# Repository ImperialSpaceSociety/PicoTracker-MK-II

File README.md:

# Pico Balloon Tracker Version 2.0

## Objectives
This Pico balloon tracker is designed to offer an easy to build and low cost entry for people who want to launch small Helium filled balloons with a small tracking payload.
Ideally, it should be able to fly around the world on board a small balloon.

## License

Hardware is Licensed under CERN OHL v.1.2 or later https://www.ohwr.org/documents/294 No warranty is provided for this documentation implied or otherwise.

Software is licensed under MIT License.

MIT License

Copyright (c) 2018 Imperial College Space Society

Derived Software  Copyright (c) 2014  Richard Meadows <richardeoin>

Permission is hereby granted, free of charge, to any person obtaining a copy of this software and associated documentation files (the "Software"), to deal in the Software without restriction, including without limitation the rights to use, copy, modify, merge, publish, distribute, sublicense, and/or sell copies of the Software, and to permit persons to whom the Software is furnished to do so, subject to the following conditions:

The above copyright notice and this permission notice shall be included in all copies or substantial portions of the Software.

THE SOFTWARE IS PROVIDED "AS IS", WITHOUT WARRANTY OF ANY KIND, EXPRESS OR IMPLIED, INCLUDING BUT NOT LIMITED TO THE WARRANTIES OF MERCHANTABILITY, FITNESS FOR A PARTICULAR PURPOSE AND NONINFRINGEMENT. IN NO EVENT SHALL THE AUTHORS OR COPYRIGHT HOLDERS BE LIABLE FOR ANY CLAIM, DAMAGES OR OTHER LIABILITY, WHETHER IN AN ACTION OF CONTRACT, TORT OR OTHERWISE, ARISING FROM, OUT OF OR IN CONNECTION WITH THE SOFTWARE OR THE USE OR OTHER DEALINGS IN THE SOFTWARE.

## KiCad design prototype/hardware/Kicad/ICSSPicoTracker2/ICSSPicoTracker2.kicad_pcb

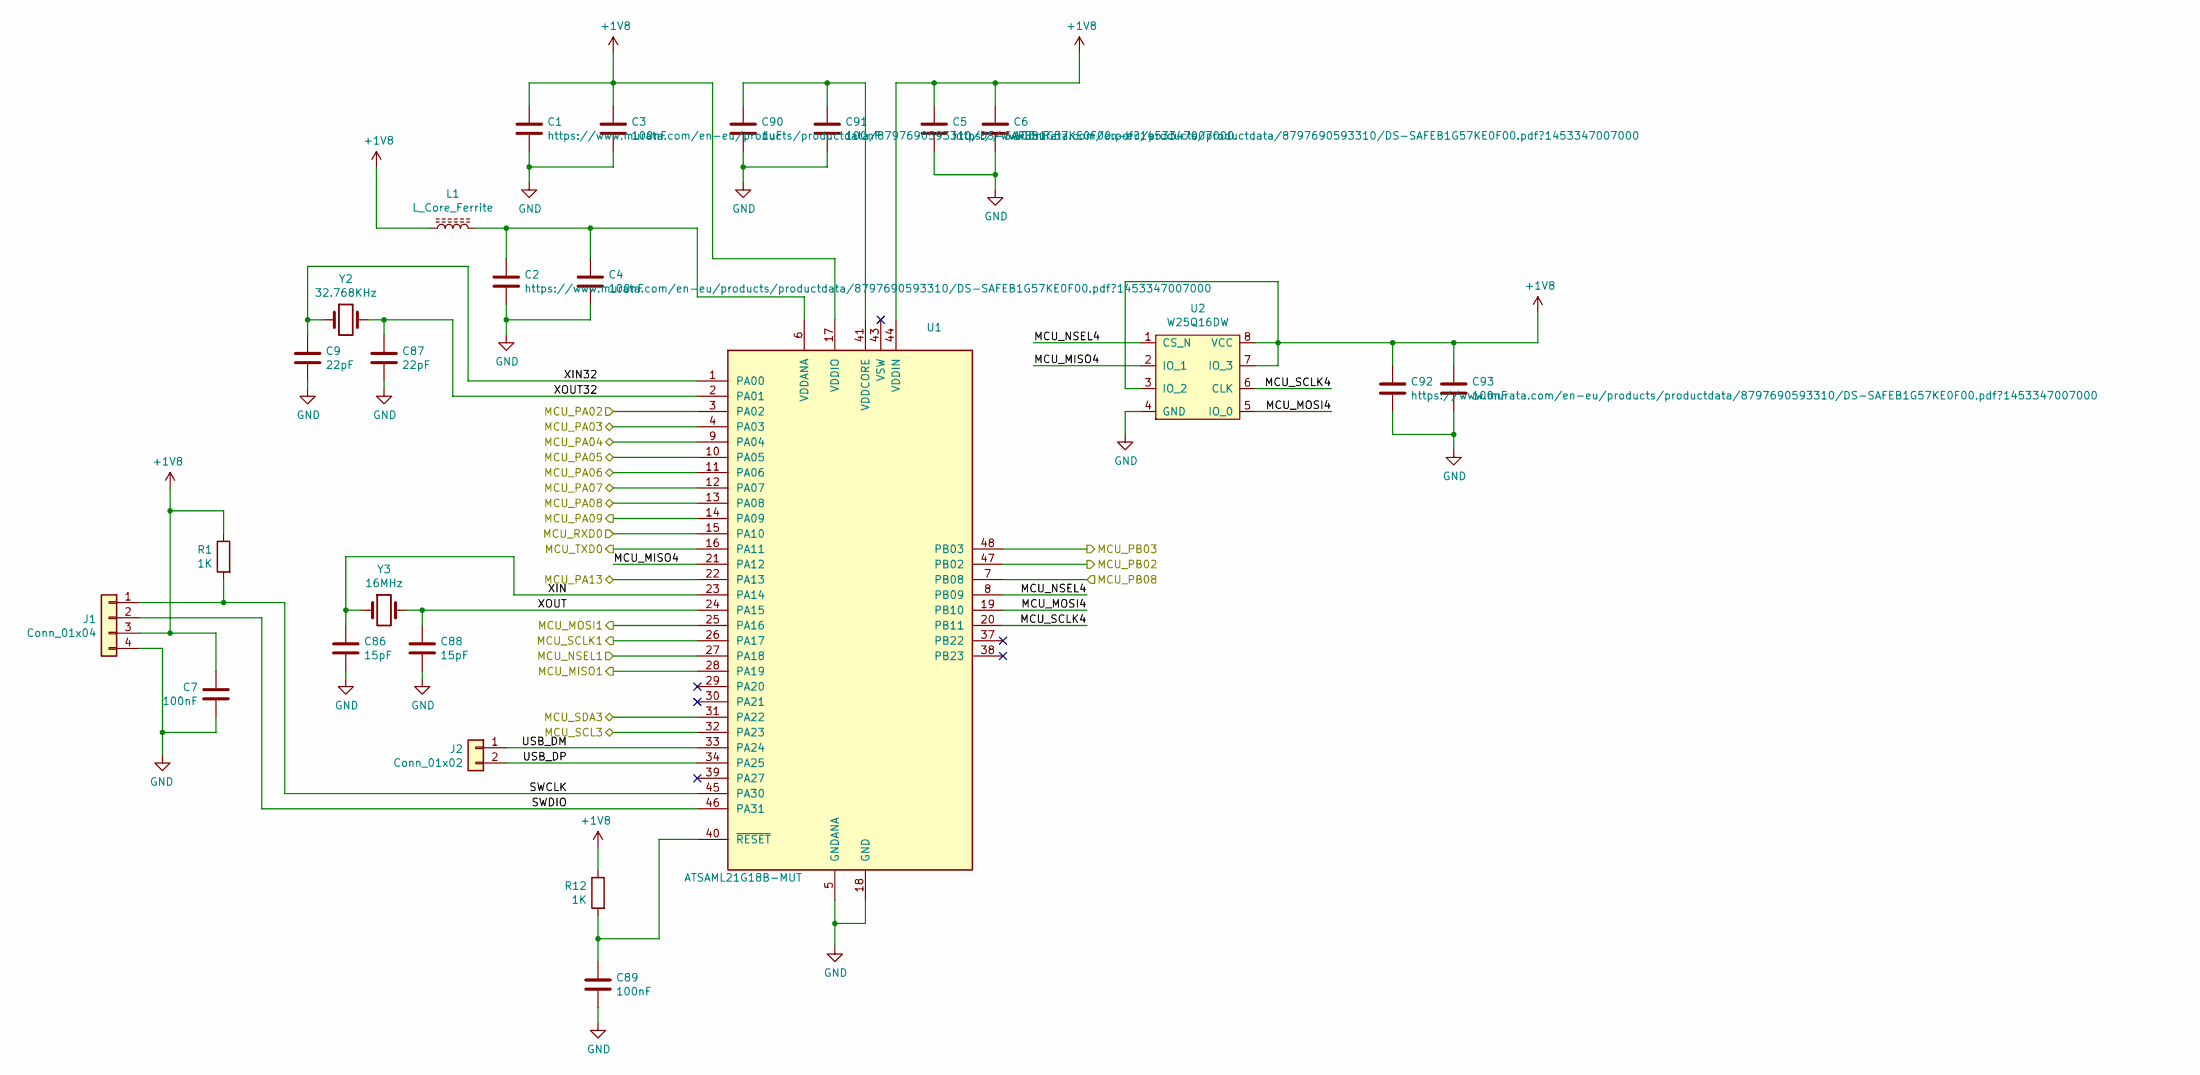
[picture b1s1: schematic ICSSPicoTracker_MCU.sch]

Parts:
C1, C2, C5, C92: https://www.murata.com/en-eu/products/productdata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; C_0603_1608Metric
C3, C4, C6, C7, C89, C91, C93: 100nF; C_0603_1608Metric
C9, C87: 22pF; C_0402_1005Metric
C86, C88: 15pF; C_0402_1005Metric
C90: 1uF; C_0603_1608Metric
J1: Conn_01x04; PinHeader_1x04_P1.00mm_Vertical
J2: Conn_01x02; PinHeader_1x02_P1.00mm_Vertical
L1: L_Core_Ferrite; L_0603_1608Metric
R1, R12: 1K; R_0603_1608Metric
U1: ATSAML21G18B-MUT; QFN-48-1EP_7x7mm_P0.5mm_EP5.15x5.15mm
U2: W25Q16DW; WSON-8-1EP_6x5mm_P1.27mm_EP3.4x4.3mm
Y2: 32.768KHz; Crystal_SMD_2012-2Pin_2.0x1.2mm
Y3: 16MHz; Crystal_SMD_2520-4Pin_2.5x2.0mm

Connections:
+1V8: C1.1, C3.1, C5.1, C6.1, C7.1, C92.1, C93.1, J1.3, L1.1, R1.1, R12.1, U1.17 (VDDIO), U1.36 (VDDIO), U1.44 (VDDIN), U2.3 (IO_2), U2.7 (IO_3), U2.8 (VCC); also elsewhere on the board
/GPS/GPS_1PPS: U1.7 (PB08); also elsewhere on the board
/GPS/GPS_NRES: U1.47 (PB02); also elsewhere on the board
/GPS/GPS_NSAFEBOOT: U1.48 (PB03); also elsewhere on the board
/GPS/GPS_RXD: U1.16 (PA11); also elsewhere on the board
/GPS/GPS_SCL: U1.32 (PA23); also elsewhere on the board
/GPS/GPS_SDA: U1.31 (PA22); also elsewhere on the board
/GPS/GPS_TXD: U1.15 (PA10); also elsewhere on the board
/MCU/MCU_MISO1: U1.28 (PA19); also elsewhere on the board
/MCU/MCU_MISO4: U1.21 (PA12), U2.2 (IO_1)
/MCU/MCU_MOSI1: U1.25 (PA16); also elsewhere on the board
/MCU/MCU_MOSI4: U1.19 (PB10), U2.5 (IO_0)
/MCU/MCU_NSEL1: U1.27 (PA18); also elsewhere on the board
/MCU/MCU_NSEL4: U1.8 (PB09), U2.1 (CS_N)
/MCU/MCU_PA02: U1.3 (PA02); also elsewhere on the board
/MCU/MCU_PA03: U1.4 (PA03); also elsewhere on the board
/MCU/MCU_PA04: U1.9 (PA04); also elsewhere on the board
/MCU/MCU_PA05: U1.10 (PA05); also elsewhere on the board
/MCU/MCU_PA06: U1.11 (PA06); also elsewhere on the board
/MCU/MCU_PA07: U1.12 (PA07); also elsewhere on the board
/MCU/MCU_PA08: U1.13 (PA08); also elsewhere on the board
/MCU/MCU_PA09: U1.14 (PA09); also elsewhere on the board
/MCU/MCU_PA13: U1.22 (PA13); also elsewhere on the board
/MCU/MCU_SCLK1: U1.26 (PA17); also elsewhere on the board
/MCU/MCU_SCLK4: U1.20 (PB11), U2.6 (CLK)
/MCU/SWCLK: J1.1, R1.2, U1.45 (PA30)
/MCU/SWDIO: J1.2, U1.46 (PA31)
/MCU/USB_DM: J2.1, U1.33 (PA24)
/MCU/USB_DP: J2.2, U1.34 (PA25)
/MCU/XIN: C86.1, U1.23 (PA14), Y3.1
/MCU/XIN32: C9.1, U1.1 (PA00), Y2.1
/MCU/XOUT: C88.1, U1.24 (PA15), Y3.2
/MCU/XOUT32: C87.1, U1.2 (PA01), Y2.2
unnamed: C2.1, C4.1, L1.2, U1.6 (VDDANA)
unnamed: C89.1, R12.2, U1.40 (~RESET)
unnamed: C90.1, C91.1, U1.41 (VDDCORE)

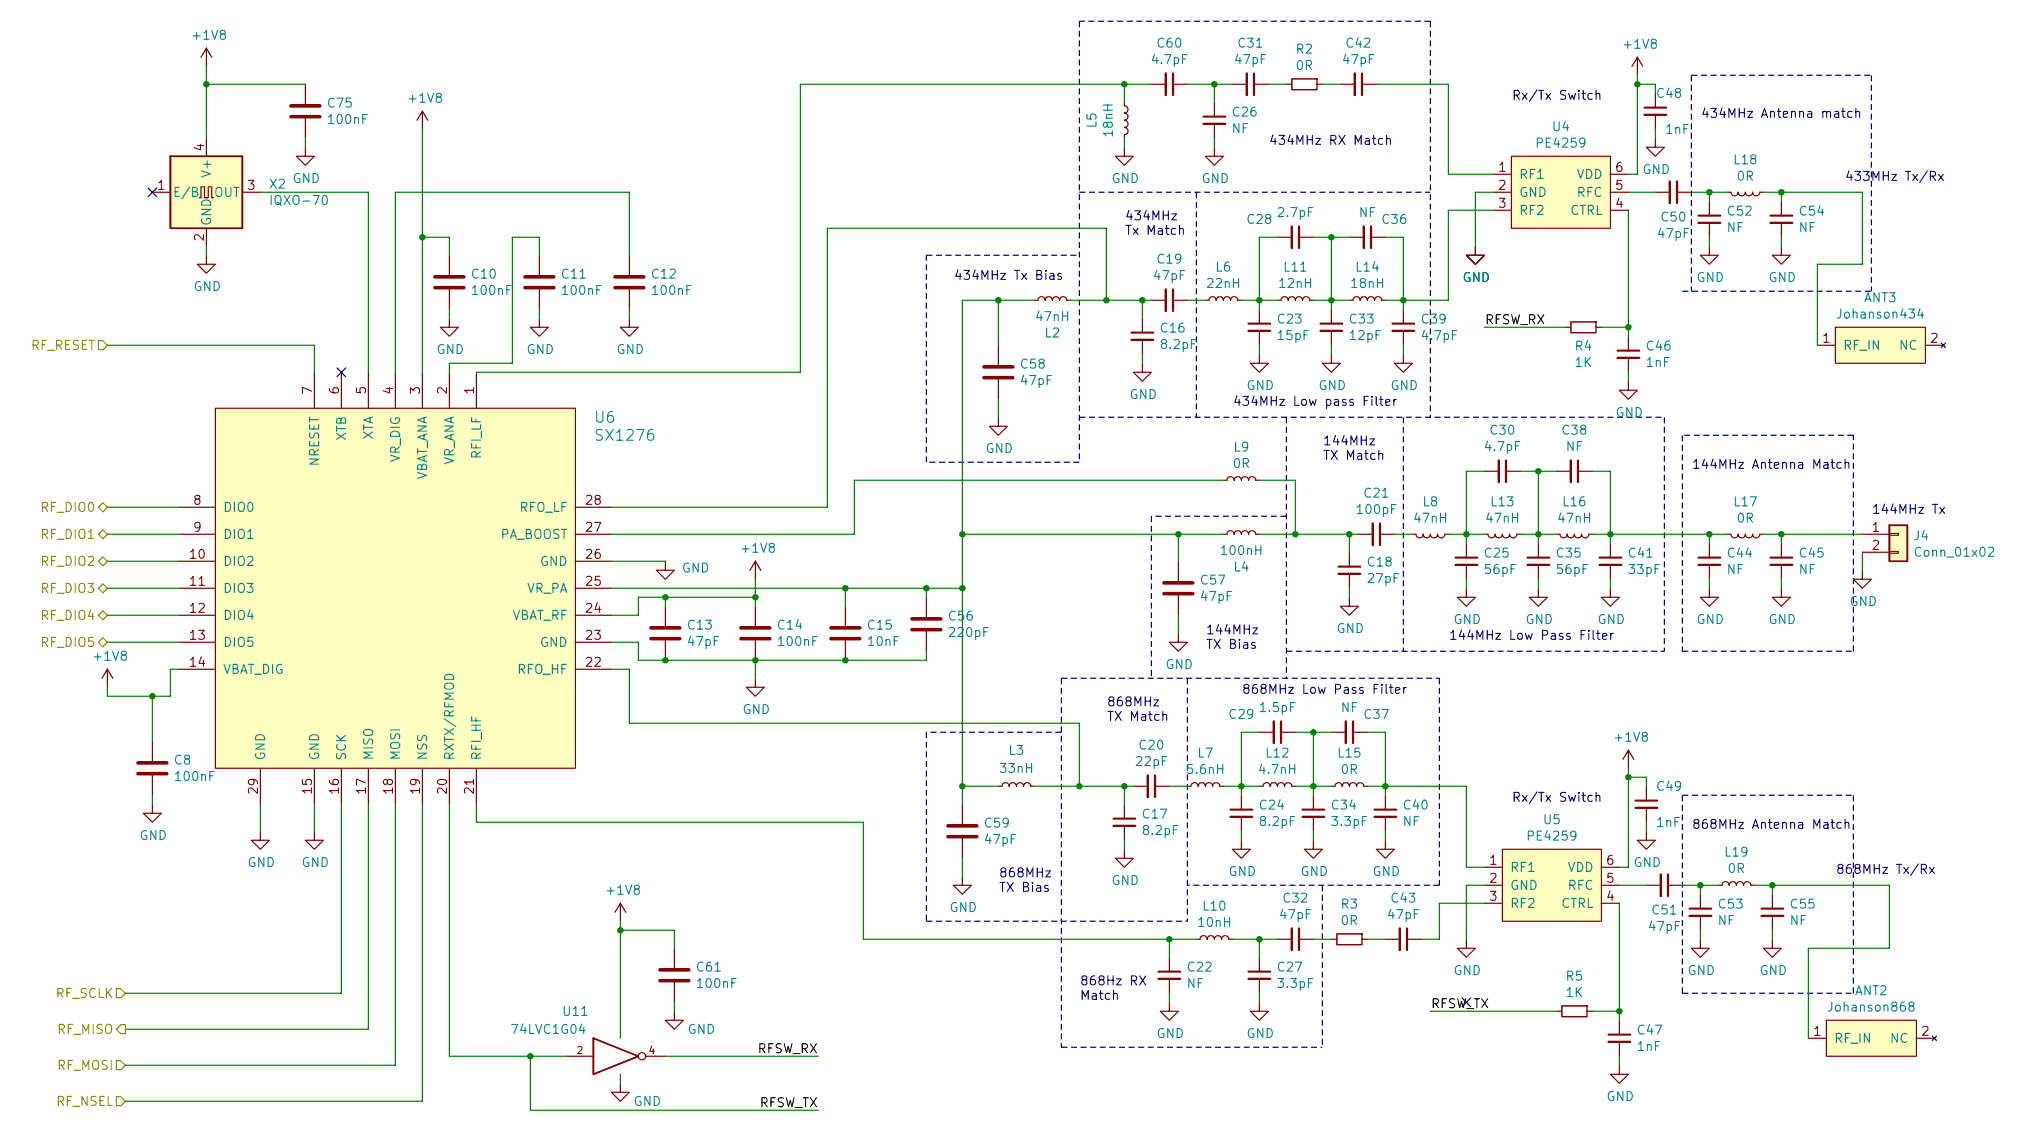
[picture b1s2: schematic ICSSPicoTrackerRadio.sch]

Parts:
ANT2: Johanson868
ANT3: Johanson434
C8, C10, C11, C12, C14, C61, C75: 100nF; C_0603_1608Metric
C13, C19, C31, C32, C42, C43, C50, C51, C57, C58, C59: 47pF; C_0402_1005Metric
C15: 10nF; C_0402_1005Metric
C16, C17, C24: 8.2pF; C_0402_1005Metric
C18: 27pF; C_0402_1005Metric
C20: 22pF; C_0402_1005Metric
C21: 100pF; C_0402_1005Metric
C22, C26, C36, C37, C38, C40, C44, C45, C52, C53, C54, C55: NF; C_0402_1005Metric
C23: 15pF; C_0402_1005Metric
C25, C35: 56pF; C_0402_1005Metric
C27, C34: 3.3pF; C_0402_1005Metric
C28: 2.7pF; C_0402_1005Metric
C29: 1.5pF; C_0402_1005Metric
C30, C39, C60: 4.7pF; C_0402_1005Metric
C33: 12pF; C_0402_1005Metric
C41: 33pF; C_0402_1005Metric
C46, C47, C48, C49: 1nF; C_0402_1005Metric
C56: 220pF; C_0402_1005Metric
J4: Conn_01x02; PinHeader_1x02_P2.54mm_Vertical
L2, L8, L13, L16: 47nH; L_0402_1005Metric
L3: 33nH; L_0402_1005Metric
L4: 100nH; L_0402_1005Metric
L5, L14: 18nH; L_0402_1005Metric
L6: 22nH; L_0402_1005Metric
L7: 5.6nH; L_0402_1005Metric
L9, L15, L17, L18, L19: 0R; L_0402_1005Metric
L10: 10nH; L_0402_1005Metric
L11: 12nH; L_0402_1005Metric
L12: 4.7nH; L_0402_1005Metric
R2, R3: 0R; R_0603_1608Metric
R4, R5: 1K; R_0603_1608Metric
U4, U5: PE4259; SOT-363_SC-70-6_Handsoldering
U6: SX1276; QFN-28-1EP_6x6mm_P0.65mm_EP4.25x4.25mm_ThermalVias
U11: 74LVC1G04; SOT-353_SC-70-5
X2: IQXO-70; Oscillator_SMD_SeikoEpson_SG210-4Pin_2.5x2.0mm

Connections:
+1V8: C8.1, C10.1, C13.1, C14.1, C48.1, C49.1, C61.1, C75.1, U4.6 (VDD), U5.6 (VDD), U6.3 (VBAT_ANA), U6.14 (VBAT_DIG), U6.24 (VBAT_RF), U11.5 (VCC), X2.4 (V+); also elsewhere on the board
/MCU/MCU_MISO1: U6.17 (MISO); also elsewhere on the board
/MCU/MCU_MOSI1: U6.18 (MOSI); also elsewhere on the board
/MCU/MCU_NSEL1: U6.19 (NSS); also elsewhere on the board
/MCU/MCU_PA03: U6.13 (DIO5); also elsewhere on the board
/MCU/MCU_PA04: U6.12 (DIO4); also elsewhere on the board
/MCU/MCU_PA05: U6.11 (DIO3); also elsewhere on the board
/MCU/MCU_PA06: U6.10 (DIO2); also elsewhere on the board
/MCU/MCU_PA07: U6.9 (DIO1); also elsewhere on the board
/MCU/MCU_PA08: U6.8 (DIO0); also elsewhere on the board
/MCU/MCU_PA09: U6.7 (NRESET); also elsewhere on the board
/MCU/MCU_SCLK1: U6.16 (SCK); also elsewhere on the board
/Telemetry Radio/RFSW_RX: R4.2, U11.4
/Telemetry Radio/RFSW_TX: R5.2, U6.20 (RXTX/RFMOD), U11.2
unnamed: ANT2.1 (RF_IN), C55.1, L19.2
unnamed: ANT3.1 (RF_IN), C54.1, L18.2
unnamed: C11.1, U6.2 (VR_ANA)
unnamed: C12.1, U6.4 (VR_DIG)
unnamed: C15.1, C56.1, C57.1, C58.1, C59.1, L2.1, L3.1, L4.1, U6.25 (VR_PA)
unnamed: C16.1, C19.2, L2.2, U6.28 (RFO_LF)
unnamed: C17.1, C20.2, L3.2, U6.22 (RFO_HF)
unnamed: C18.1, C21.2, L4.2, L9.2
unnamed: C19.1, L6.1
unnamed: C20.1, L7.1
unnamed: C21.1, L8.1
unnamed: C22.1, L10.1, U6.21 (RFI_HF)
unnamed: C23.1, C28.2, L6.2, L11.1
unnamed: C24.1, C29.2, L7.2, L12.1
unnamed: C25.1, C30.2, L8.2, L13.1
unnamed: C26.1, C31.2, C60.1
unnamed: C27.1, C32.2, L10.2
unnamed: C28.1, C33.1, C36.2, L11.2, L14.1
unnamed: C29.1, C34.1, C37.2, L12.2, L15.1
unnamed: C30.1, C35.1, C38.2, L13.2, L16.1
unnamed: C31.1, R2.2
unnamed: C32.1, R3.2
unnamed: C36.1, C39.1, L14.2, U4.3 (RF2)
unnamed: C37.1, C40.1, L15.2, U5.1 (RF1)
unnamed: C38.1, C41.1, C44.1, L16.2, L17.2
unnamed: C42.1, U4.1 (RF1)
unnamed: C42.2, R2.1
unnamed: C43.1, U5.3 (RF2)
unnamed: C43.2, R3.1
unnamed: C45.1, J4.1, L17.1
unnamed: C46.1, R4.1, U4.4 (CTRL)
unnamed: C47.1, R5.1, U5.4 (CTRL)
unnamed: C50.1, C52.1, L18.1
unnamed: C50.2, U4.5 (RFC)
unnamed: C51.1, C53.1, L19.1
unnamed: C51.2, U5.5 (RFC)
unnamed: C60.2, L5.1, U6.1 (RFI_LF)
unnamed: L9.1, U6.27 (PA_BOOST)
unnamed: U6.5 (XTA), X2.3 (OUT)

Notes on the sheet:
144MHz Tx
433MHz Tx/Rx
868MHz Tx/Rx
144MHz Low Pass Filter
144MHz Antenna Match
144MHz TX Bias
144MHz TX Match
Rx/Tx Switch
868MHz TX Bias
868MHz TX Match
868MHz Low Pass Filter
868MHz Antenna Match
434MHz RX Match
434MHz Tx Bias
434MHz Tx Match
434MHz Low pass Filter
434MHz Antenna match
868Hz RX Match

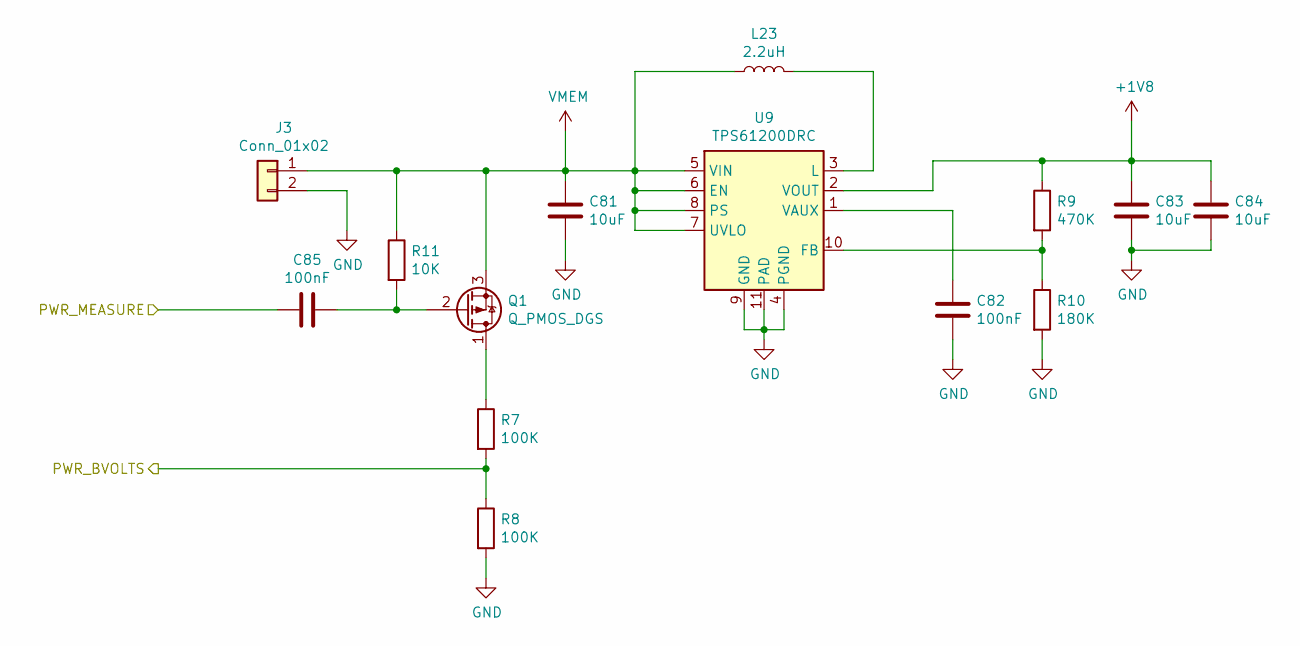
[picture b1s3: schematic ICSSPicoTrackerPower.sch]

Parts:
C81, C83, C84: 10uF; C_0603_1608Metric
C82, C85: 100nF; C_0603_1608Metric
J3: Conn_01x02; PinHeader_1x02_P1.00mm_Vertical
L23: 2.2uH; L_Taiyo-Yuden_NR-30xx
Q1: Q_PMOS_DGS; SOT-23
R7, R8: 100K; R_0603_1608Metric
R9: 470K; R_0603_1608Metric
R10: 180K; R_0603_1608Metric
R11: 10K; R_0603_1608Metric
U9: TPS61200DRC; Texas_S-PVSON-N10_ThermalVias

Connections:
+1V8: C83.1, C84.1, R9.1, U9.2 (VOUT); also elsewhere on the board
/MCU/MCU_PA02: R7.2, R8.1; also elsewhere on the board
/MCU/MCU_PA13: C85.1; also elsewhere on the board
unnamed: C82.1, U9.1 (VAUX)
unnamed: C85.2, Q1.2 (G), R11.2
unnamed: L23.2, U9.3 (L)
unnamed: Q1.1 (D), R7.1
unnamed: R9.2, R10.1, U9.10 (FB)
VMEM: C81.1, J3.1, L23.1, Q1.3 (S), R11.1, U9.5 (VIN), U9.6 (EN), U9.7 (UVLO), U9.8 (PS); also elsewhere on the board

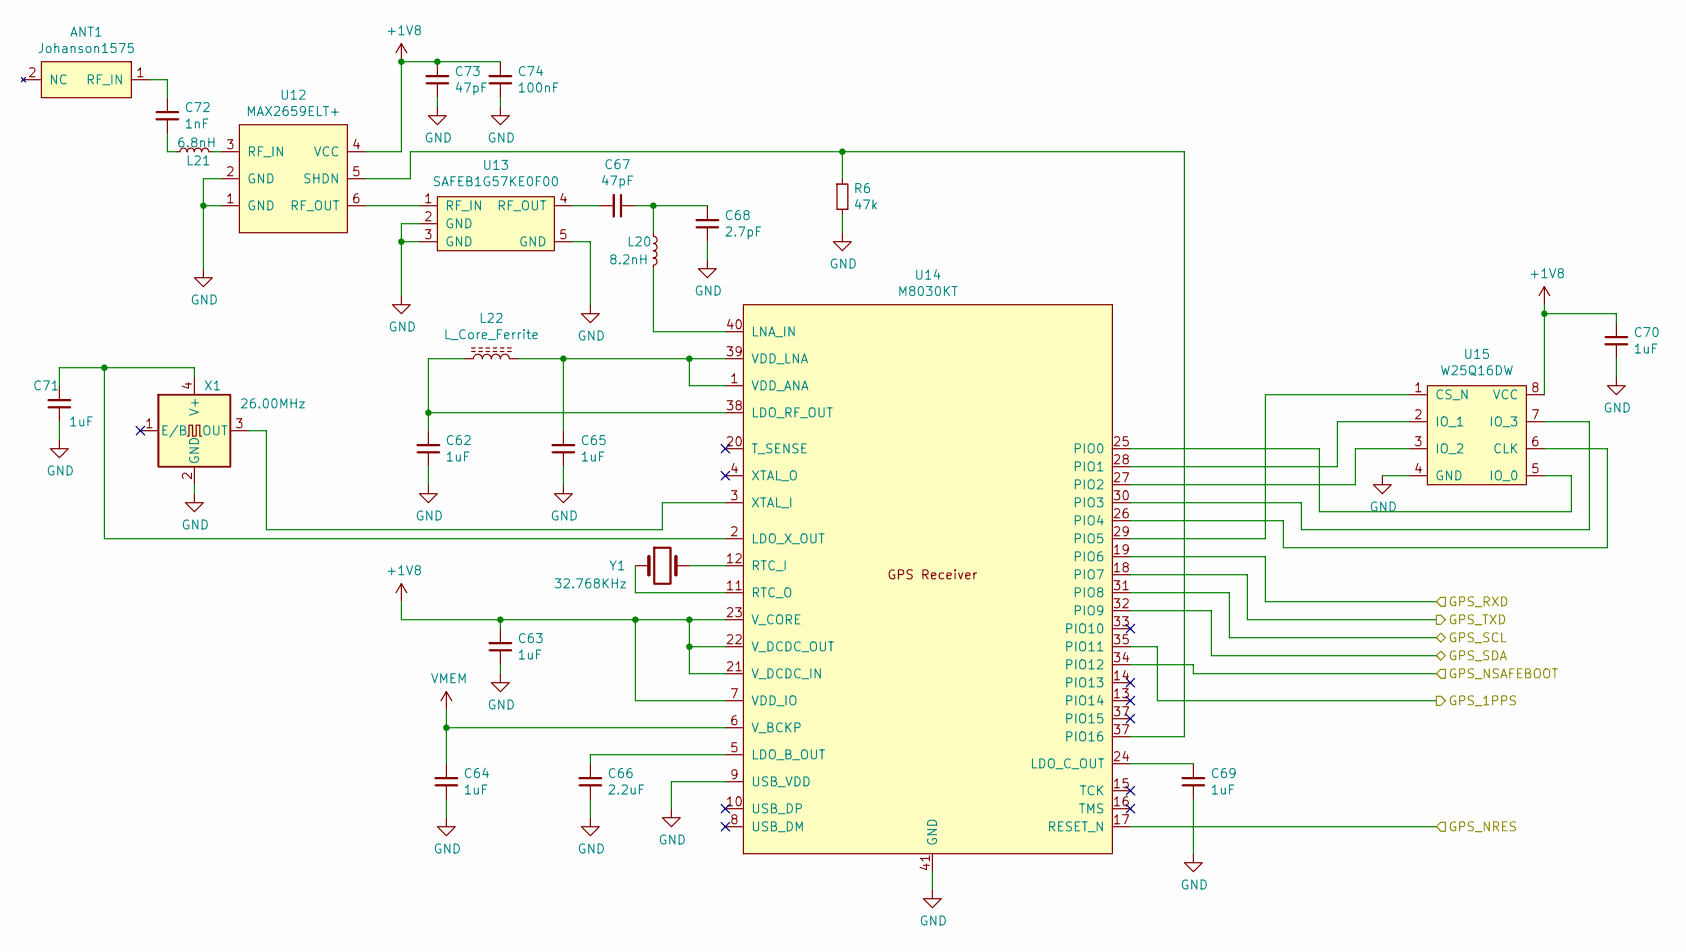
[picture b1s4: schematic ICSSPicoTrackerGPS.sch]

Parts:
ANT1: Johanson1575
C62, C63, C64, C65, C69, C70, C71: 1uF; C_0603_1608Metric
C66: 2.2uF; C_0603_1608Metric
C67, C73: 47pF; C_0402_1005Metric
C68: 2.7pF; C_0402_1005Metric
C72: 1nF; C_0402_1005Metric
C74: 100nF; C_0603_1608Metric
L20: 8.2nH; L_0402_1005Metric
L21: 6.8nH; L_0402_1005Metric
L22: L_Core_Ferrite; L_0603_1608Metric
R6: 47k; R_0603_1608Metric
U12: MAX2659ELT+; uDFN-6_1.0x1.5mm_P0.5mm
U13: SAFEB1G57KE0F00; Murata SAFE
U14: M8030KT; QFN-40-1EP_5x5mm_P0.4mm_EP3.6x3.6mm_ThermalVias
U15: W25Q16DW; WSON-8-1EP_6x5mm_P1.27mm_EP3.4x4.3mm
X1: 26.00MHz; Oscillator_SMD_SeikoEpson_SG210-4Pin_2.5x2.0mm
Y1: 32.768KHz; Crystal_SMD_2012-2Pin_2.0x1.2mm

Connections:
+1V8: C63.2, C70.1, C73.2, C74.2, U12.4 (VCC), U14.7 (VDD_IO), U14.21 (V_DCDC_IN), U14.22 (V_DCDC_OUT), U14.23 (V_CORE), U15.8 (VCC); also elsewhere on the board
/GPS/GPS_1PPS: U14.35 (PIO11); also elsewhere on the board
/GPS/GPS_NRES: U14.17 (RESET_N); also elsewhere on the board
/GPS/GPS_NSAFEBOOT: U14.34 (PIO12); also elsewhere on the board
/GPS/GPS_RXD: U14.19 (PIO6); also elsewhere on the board
/GPS/GPS_SCL: U14.31 (PIO8); also elsewhere on the board
/GPS/GPS_SDA: U14.32 (PIO9); also elsewhere on the board
/GPS/GPS_TXD: U14.18 (PIO7); also elsewhere on the board
unnamed: ANT1.1 (RF_IN), C72.1
unnamed: C62.2, L22.1, U14.38 (LDO_RF_OUT)
unnamed: C65.2, L22.2, U14.1 (VDD_ANA), U14.39 (VDD_LNA)
unnamed: C66.2, U14.5 (LDO_B_OUT)
unnamed: C67.1, C68.2, L20.1
unnamed: C67.2, U13.4 (RF_OUT)
unnamed: C69.2, U14.24 (LDO_C_OUT)
unnamed: C71.2, U14.2 (LDO_X_OUT), X1.4 (V+)
unnamed: C72.2, L21.2
unnamed: L20.2, U14.40 (LNA_IN)
unnamed: L21.1, U12.3 (RF_IN)
unnamed: U12.6 (RF_OUT), U13.1 (RF_IN)
unnamed: U14.3 (XTAL_I), X1.3 (OUT)
unnamed: U14.11 (RTC_O), Y1.1
unnamed: U14.12 (RTC_I), Y1.2
unnamed: U14.25 (PIO0), U15.5 (IO_0)
unnamed: U14.26 (PIO4), U15.6 (CLK)
unnamed: U14.27 (PIO2), U15.3 (IO_2)
unnamed: U14.28 (PIO1), U15.2 (IO_1)
unnamed: U14.29 (PIO5), U15.1 (CS_N)
unnamed: U14.30 (PIO3), U15.7 (IO_3)
VMEM: C64.2, U14.6 (V_BCKP); also elsewhere on the board

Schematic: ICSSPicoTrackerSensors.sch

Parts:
U7: MPU-9150; InvenSense_QFN-24_4x4mm_P0.5mm
U8: MS5607-02BA; LGA-8_3x5mm_P1.25mm
U9: APDS-9306; Broadcom_LGA-8_2x2mm_P0.53mm
U10: SHT1x

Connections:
+1V8: U7.3 (VDD), U7.8 (VDDIO), U7.13 (VDD), U8.1 (VDD), U8.2 (PS); also elsewhere on the board
/GPS/GPS_SCL: U7.23 (SCL), U8.8 (SCLK); also elsewhere on the board
/GPS/GPS_SDA: U7.24 (SDA), U8.7 (SDI/SDA); also elsewhere on the board
unnamed 85: U7.10 (REGOUT); also elsewhere on the board
unnamed 86: U7.20 (CPOUT); also elsewhere on the board

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
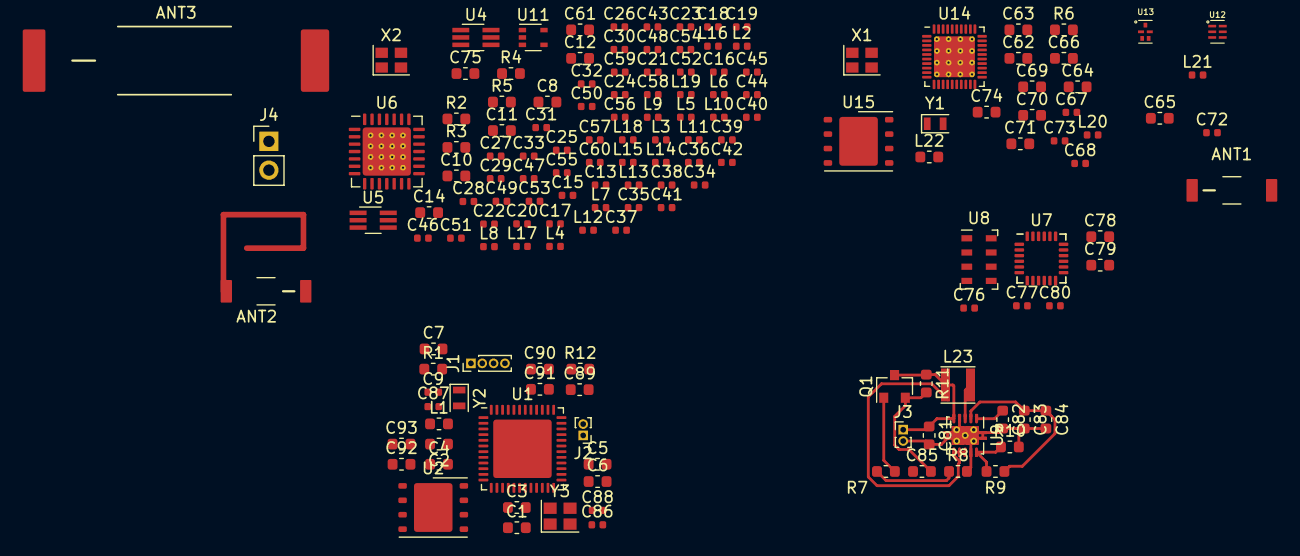
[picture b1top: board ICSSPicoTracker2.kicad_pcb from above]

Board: 2 copper layers, 154 parts (0 on the bottom side), 108 nets.

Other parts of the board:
C76: 10nF; C_0402_1005Metric
C77: 220nF; C_0402_1005Metric
C78, C79: 100nF; C_0603_1608Metric
C80: 2,2nF; C_0402_1005Metric

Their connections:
+1V8: C76.1, C77.1, C78.1; also elsewhere on the board
unnamed 85: C79.1; also elsewhere on the board
unnamed 86: C80.1; also elsewhere on the board

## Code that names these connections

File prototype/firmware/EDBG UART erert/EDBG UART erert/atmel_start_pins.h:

/*
 * Code generated from Atmel Start.
 *
 * This file will be overwritten when reconfiguring your Atmel Start project.
 * Please copy examples or other code you want to keep to a separate file
 * to avoid losing it when reconfiguring.
 */
#ifndef ATMEL_START_PINS_H_INCLUDED
#define ATMEL_START_PINS_H_INCLUDED

#include <hal_gpio.h>

// SAML21 has 9 pin functions

#define GPIO_PIN_FUNCTION_A 0
#define GPIO_PIN_FUNCTION_B 1
#define GPIO_PIN_FUNCTION_C 2
#define GPIO_PIN_FUNCTION_D 3
#define GPIO_PIN_FUNCTION_E 4
#define GPIO_PIN_FUNCTION_F 5
#define GPIO_PIN_FUNCTION_G 6
#define GPIO_PIN_FUNCTION_H 7
#define GPIO_PIN_FUNCTION_I 8

#define PA08 GPIO(GPIO_PORTA, 8)
#define PA09 GPIO(GPIO_PORTA, 9)
#define PA18 GPIO(GPIO_PORTA, 18)
#define PA19 GPIO(GPIO_PORTA, 19)
#define PA22 GPIO(GPIO_PORTA, 22)
#define PA23 GPIO(GPIO_PORTA, 23)
#define LED0 GPIO(GPIO_PORTB, 10)
#define PB16 GPIO(GPIO_PORTB, 16)
#define PB22 GPIO(GPIO_PORTB, 22)
#define PB23 GPIO(GPIO_PORTB, 23)

#endif // ATMEL_START_PINS_H_INCLUDED

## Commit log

2019-05-05 Create prototype folder
    New folder for dev. board prototype
2019-05-06 Prototype Hardware Schematic
2019-05-06 add .gitignore
2019-05-06 Firmware examples
2019-05-06 Added references
    References for BME280, RFM95W, Lora
2019-05-07 Add RFM95 project skeleton
2019-05-08 Add BaseStation.md
2019-05-08 RFM98W Work in progress!
2019-05-10 Sort out naming mistake RFM98W
    Hope I didn't break it all!
2019-05-11 Added another GPS passthrough utility, using asyc UART
2019-05-12 Update RFM98W
    Transmitting, but rubbish
2019-05-13 This is sending reasonable 50 baud RTTY FSK
    Need to sort out eh loss of first character and the proper signalling of status
2019-05-13 Update Prototype schematic
2019-05-15 Added the basic tracker project. It is in folder 'EDBG UART erert'
    It is in folder 'EDBG UART erert'. I used that directory name earlier but now I don't know how to change it to something more descriptive
2019-05-18 Added the radio libraries to the Basic tracker
2019-05-24 archiving this state
2019-05-25 Got the transmissions working
2019-06-28 Fixed the bug with the checksum errors
2019-07-23 Add Kicad file
2019-07-24 Add Spice Files
    Add Spice directory and add files for radio telemetry filter simulations
2019-08-03 Add GPS, Remove FM
2019-08-17 Updated Scehematics and Footprints
2019-08-18 Add Antenna footprints
2019-08-20 put in the drawings of the tracker
2019-08-21 Smaller Antenna and try some layouts
2019-08-22 Fixed library table
2019-08-24 Some more ERC fixes
2019-08-24 Fix outstanding erc errors
2019-09-05 fully wired up the LD3985 LDO
2019-09-07 Revert "fully wired up the LD3985 LDO"
    This reverts commit 04a440f3a08b8c97db9d4cc44cd5207f890db50a.
2019-09-17 some backup files were generated
2019-09-20 Revert "Fix outstanding erc errors"
    This reverts commit a3499ea02454ddf107046470f2c267134ce277ae.
